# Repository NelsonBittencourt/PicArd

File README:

These are the KiCad files for a Nano version of the programer

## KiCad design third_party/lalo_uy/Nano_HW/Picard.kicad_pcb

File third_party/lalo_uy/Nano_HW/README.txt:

These are the KICad files of a Nano version of the programer

@NelsonBittencourt note: 
There is an error in this PicArd Nano version. The Nano board 5V pin is an input pin, not an output. Thus, when using USB to power the board, the 5V pin will provide (5V-{diode voltage drop}). To correct this, connect the PicArd 5V pin directly to USB 5V rail.

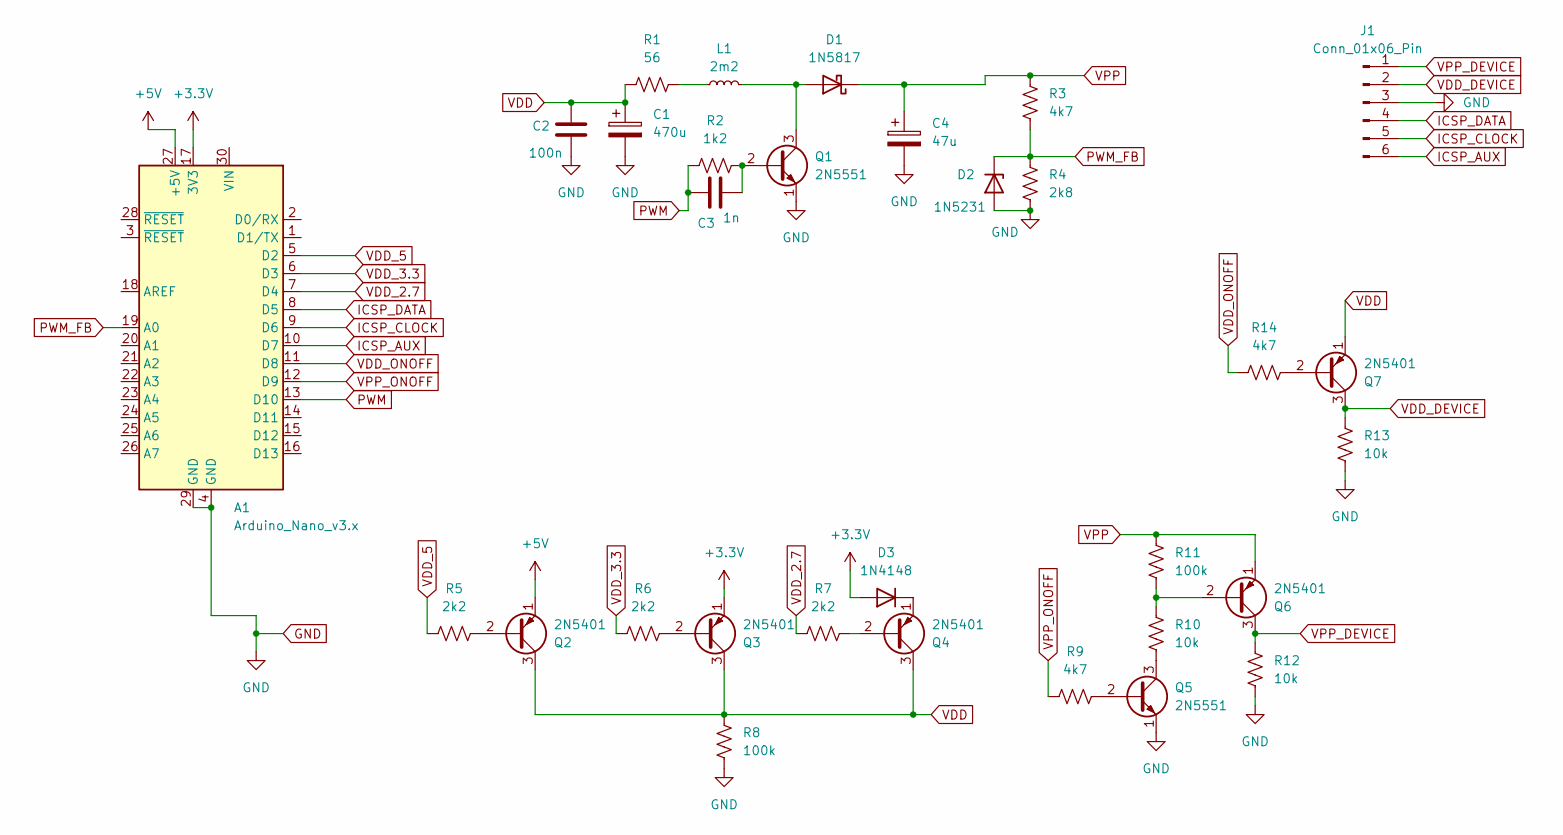
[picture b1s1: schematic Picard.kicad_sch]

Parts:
A1: Arduino_Nano_v3.x; Arduino_Nano
C1: 470u; CP_Radial_D10.0mm_P5.00mm
C2: 100n; C_Axial_L3.8mm_D2.6mm_P7.50mm_Horizontal
C3: 1n; C_Axial_L3.8mm_D2.6mm_P7.50mm_Horizontal
C4: 47u; CP_Radial_D5.0mm_P2.50mm
D1: 1N5817; D_DO-41_SOD81_P10.16mm_Horizontal
D2: 1N5231; D_DO-201_P15.24mm_Horizontal
D3: 1N4148; D_DO-35_SOD27_P7.62mm_Horizontal
J1: Conn_01x06_Pin; PinHeader_1x06_P2.54mm_Vertical
L1: 2m2; L_Axial_L5.0mm_D3.6mm_P10.00mm_Horizontal_Murata_BL01RN1A2A2
Q1, Q5: 2N5551; TO-92_Inline_Wide
Q2, Q3, Q4, Q6, Q7: 2N5401; TO-92_Inline_Wide
R1: 56; R_Axial_DIN0207_L6.3mm_D2.5mm_P10.16mm_Horizontal
R2: 1k2; R_Axial_DIN0207_L6.3mm_D2.5mm_P10.16mm_Horizontal
R3, R9, R14: 4k7; R_Axial_DIN0207_L6.3mm_D2.5mm_P10.16mm_Horizontal
R4: 2k8; R_Axial_DIN0207_L6.3mm_D2.5mm_P10.16mm_Horizontal
R5, R6, R7: 2k2; R_Axial_DIN0207_L6.3mm_D2.5mm_P10.16mm_Horizontal
R8, R11: 100k; R_Axial_DIN0207_L6.3mm_D2.5mm_P10.16mm_Horizontal
R10, R12, R13: 10k; R_Axial_DIN0207_L6.3mm_D2.5mm_P10.16mm_Horizontal

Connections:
+3.3V: A1.17 (3V3), D3.2 (A), Q3.1 (E)
+5V: A1.27 (+5V), Q2.1 (E)
GND: A1.4 (GND), A1.29 (GND), C1.2, C2.2, C4.2, D2.2 (A), J1.3, Q1.1 (E), Q5.1 (E), R4.1, R8.1, R12.1, R13.1
ICSP_AUX: A1.10 (D7), J1.6
ICSP_CLOCK: A1.9 (D6), J1.5
ICSP_DATA: A1.8 (D5), J1.4
unnamed: D1.2 (A), L1.2, Q1.3 (C)
unnamed: D3.1 (K), Q4.1 (E)
unnamed: L1.1, R1.2
unnamed: C3.2, Q1.2 (B), R2.2
unnamed: Q2.2 (B), R5.2
unnamed: Q3.2 (B), R6.2
unnamed: Q4.2 (B), R7.2
unnamed: Q5.2 (B), R9.2
unnamed: Q5.3 (C), R10.1
unnamed: Q6.2 (B), R10.2, R11.1
unnamed: Q7.2 (B), R14.2
PWM: A1.13 (D10), C3.1, R2.1
PWM_FB: A1.19 (A0), D2.1 (K), R3.1, R4.2
VDD: C1.1, C2.1, Q2.3 (C), Q3.3 (C), Q4.3 (C), Q7.1 (E), R1.1, R8.2
VDD_2.7: A1.7 (D4), R7.1
VDD_3.3: A1.6 (D3), R6.1
VDD_5: A1.5 (D2), R5.1
VDD_DEVICE: J1.2, Q7.3 (C), R13.2
VDD_ONOFF: A1.11 (D8), R14.1
VPP: C4.1, D1.1 (K), Q6.1 (E), R3.2, R11.2
VPP_DEVICE: J1.1, Q6.3 (C), R12.2
VPP_ONOFF: A1.12 (D9), R9.1

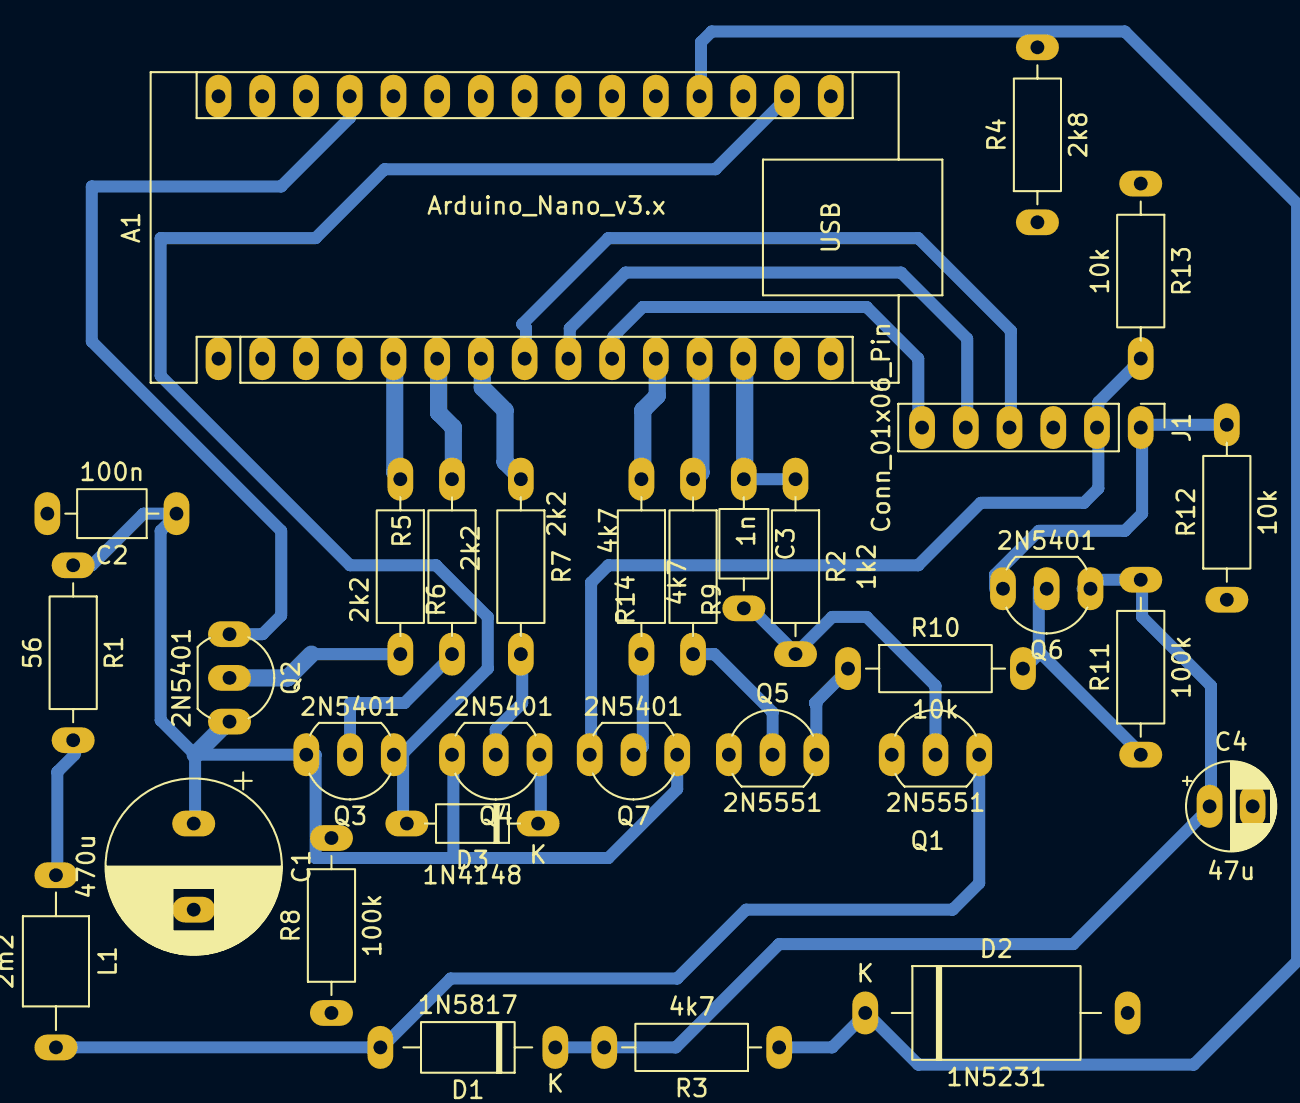
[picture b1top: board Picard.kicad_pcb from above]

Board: 2 copper layers, 31 parts (0 on the bottom side), 28 nets.

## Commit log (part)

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2024-05-20 Update LICENSE
2025-11-14 version 0.41
2025-11-14 Create docs
2025-11-14 Create test
2025-11-14 Create null
2026-02-19 Update for PicArd GUI version
2026-02-19 Linux version warning about USB access
2026-02-23 Tmp images to test
2026-02-23 Arduino Uno Shield - Gerber Files
2026-02-23 Added Arduino Uno Shield Gerber Files
2026-04-09 v042
    Changes:
    -PWM output pin from D11 to D10 and
    -Footprints (R2, R10 e T4).
2026-04-09 v042
    Changes:
    -PWM frequency (from 62.5kHz to 125kHz);
    -New PID parameters;
    -Anti-windup;
    -Feed-back voltage new scan time and
    -Minor changes for increase code performance.
2026-04-09 0.42
